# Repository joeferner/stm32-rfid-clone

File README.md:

# STM32 RFID Reader / Writer

Currently only reading is working.

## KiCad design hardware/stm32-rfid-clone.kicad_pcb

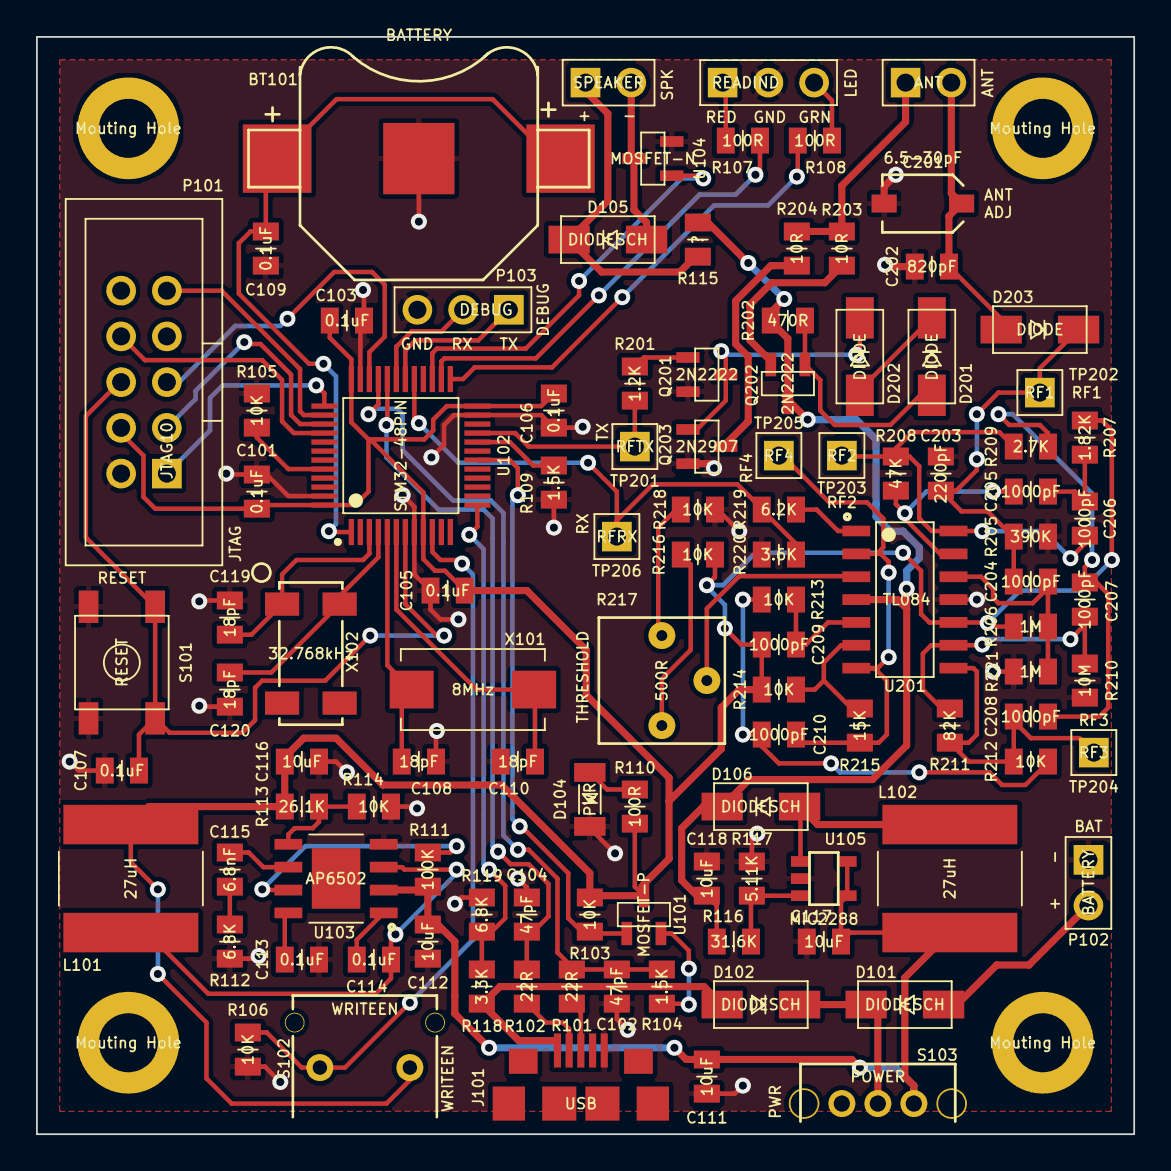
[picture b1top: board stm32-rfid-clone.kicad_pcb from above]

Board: 2 copper layers, 61.0 x 61.0 mm, 112 parts (0 on the bottom side), 73 nets.

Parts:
BT101: BATTERY; KEYSTONE-3000
C101, C103, C105, C106, C107, C109, C113, C114: 0.1uF; CAPC2012X100N
C102, C104: 47pF; CAPC2012X100N
C108, C110, C119, C120: 18pF; CAPC2012X100N
C111, C112, C116, C117, C118: 10uF; CAPC2012X100N
C115: 6.8nF; CAPC2012X100N
C201: 6.5-30pF; MURATA-TZC3
C202: 820pF; CAPC2012X100N
C203: 2200pF; CAPC2012X100N
C204, C205, C206, C207, C208, C209, C210: 1000pF; CAPC2012X100N
D101, D102, D105, D106: DIODESCH; DIOM5226X220N
D104: PWR; LEDC3216X100N
D201, D202, D203: DIODE; DIOM5226X220N
J101: USB; JST_UB-MC5BR3-SD204-4S-NMP
L101, L102: 27uH; IND_ASPI-8040S-680M-T
M101, M102, M103, M104: Mouting Hole; MTGNP565H328Z565P
P101: JTAG10; SHDRV10W66P254_2X5_2035X870X609P
P102: BATTERY; HDRV2W66P254_1X2_508X249X838P
P103: DEBUG; HDRV3W66P254_1X3_762X249X838P
P104: READIND; HDRV3W66P254_1X3_762X249X838P
P105: SPEAKER; HDRV2W66P254_1X2_508X249X838P
P201: ANT; HDRV2W66P254_1X2_508X249X838P
Q201, Q202: 2N2222; SOT95P237X112_123-3N
Q203: 2N2907; SOT95P237X112_123-3N
R101, R102: 22R; RESC2012X100N
R103, R105, R106, R114, R212, R213, R214, R216, R218: 10K; RESC2012X100N
R104, R109: 1.5K; RESC2012X100N
R107, R108, R110: 100R; RESC2012X100N
R111: 100K; RESC2012X100N
R112, R119: 6.8K; RESC2012X100N
R113: 26.1K; RESC2012X100N
R115: ?; RESC2012X100N
R116: 31.6K; RESC2012X100N
R117: 5.11K; RESC2012X100N
R118: 3.3K; RESC2012X100N
R201: 1.2K; RESC2012X100N
R202: 470R; RESC2012X100N
R203, R204: 10R; RESC2012X100N
R205: 390K; RESC2012X100N
R206, R221: 1M; RESC2012X100N
R207: 1.82K; RESC2012X100N
R208: 47K; RESC2012X100N
R209: 2.7K; RESC2012X100N
R210: 10M; RESC2012X100N
R211: 82K; RESC2012X100N
R215: 15K; RESC2012X100N
R217: 500R; COPAL-CT6EP
R219: 6.2K; RESC2012X100N
R220: 3.6K; RESC2012X100N
S101: RESET; CKCOMP-PTS525SM10SMTR
S102: WRITEEN; APEM-MJTP1129B
S103: POWER; CKCOMP-OS102011MA1QN1
TP201: RFTX; HDRV1W66P254_1X1_254X249X838P
TP202: RF1; HDRV1W66P254_1X1_254X249X838P
TP203: RF2; HDRV1W66P254_1X1_254X249X838P
TP204: RF3; HDRV1W66P254_1X1_254X249X838P
TP205: RF4; HDRV1W66P254_1X1_254X249X838P
TP206: RFRX; HDRV1W66P254_1X1_254X249X838P
U101: MOSFET-P; SOT95P237X112_123-3N
U102: STM32-48PIN; QFP50P900X900X160-48N
U103: AP6502; SOIC127P600X150-9N
U104: MOSFET-N; SOT95P237X112_123-3N
U105: MIC2288; SOT95P280X100-5N
U201: TL084; SOIC127P600X175-14N
X101: 8MHz; XTAL8045X200N
X102: 32.768kHz; SOJ550P370X240-4N

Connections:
+3.3V: C101.1, C103.1, C105.1, C106.1, C116.1, C209.1, L101.1, P101.4, R103.1, R110.1, R113.1, R206.1, R207.1, R214.2, R216.1, S102.1, U101.3, U102.9, U102.24, U102.36, U102.48, U201.10
+9V: C118.1, D106.2, Q202.3, R115.1, R116.1, R202.1, U201.4
/BEEP: U102.27, U104.1
/JNTRST: P101.8, U102.40
/JTCK: P101.1, U102.37
/JTDI: P101.9, U102.38
/JTDO: P101.3, U102.39
/JTMS: P101.5, U102.34
/LEDGRN: R108.1, U102.25
/LEDRED: R107.1, U102.26
/RF/RX: R219.2, R220.1, TP206.1, U102.29
/RF/TX: R201.2, TP201.1, U102.21
/USARTRX: P103.2, U102.31
/USARTTX: P103.1, U102.30
/USBDET: R118.2, R119.1, U102.13
/USBDIS: R103.2, U101.1, U102.18
/USBDM: C104.1, R102.1, U102.32
/USBDP: C102.1, R101.1, R104.2, U102.33
/VBAT: BT101.1, C109.1, U102.1
/VIN: C111.1, C112.1, C117.1, L102.2, R111.1, S103.3, U103.2, U105.4, U105.5
/VUSB: D102.1, J101.1, R118.1
/WRITEEN: R106.1, S102.2, U102.10
/nRST: C107.1, P101.6, S101.3, S101.4, U102.7
GNDPWR: BT101.2, C101.2, C102.2, C103.2, C104.2, C105.2, C106.2, C107.2, C108.2, C109.2, C110.2, C111.2, C112.2, C113.2, C116.2, C117.2, C118.2, C119.2, C120.2, C201.2, C202.2, C203.2, D104.2, J101.5, P101.2, P102.1, P103.3, P104.2, Q201.2, Q203.2, R105.2, R106.2, R109.2, R112.2, R114.2, R117.2, R119.2, R205.2, R210.1, R218.2, R220.2, R221.2, S101.1, S101.2, U102.8, U102.23, U102.35, U102.47, U103.4, U104.2, U105.2, U201.11
unnamed: C108.1, U102.5, X101.1
unnamed: C110.1, U102.6, X101.2
unnamed: C113.1, U103.8
unnamed: C114.1, U103.1
unnamed: C114.2, L101.2, U103.3
unnamed: C115.1, U103.6
unnamed: C115.2, R112.1
unnamed: C119.1, U102.3, X102.1
unnamed: C120.1, U102.4, X102.4
unnamed: C201.1, C202.1, D203.1, P201.2
unnamed: C203.1, C204.1, D203.2, R205.1, TP202.1
unnamed: C204.2, R206.2, R221.1, U201.12
unnamed: C205.1, R208.1, U201.13
unnamed: C205.2, C206.1, R207.2
unnamed: C206.2, R208.2, R209.1, TP203.1, U201.14
unnamed: C207.1, C208.1, R209.2
unnamed: C207.2, R210.2, R211.1, U201.9
unnamed: C208.2, R211.2, R212.1, TP204.1, U201.8
unnamed: C209.2, R213.2, U201.5
unnamed: C210.1, R212.2, R213.1
unnamed: C210.2, R215.1, TP205.1, U201.2, U201.7
unnamed: D101.1, P102.2
unnamed: D101.2, D102.2, S103.2
unnamed: D104.1, R110.2
unnamed: D105.1, P105.2, U104.3
unnamed: D105.2, P105.1, R115.2
unnamed: D106.1, L102.1, U105.1
unnamed: D201.1, Q202.1, R202.2
unnamed: D201.2, D202.1
unnamed: D202.2, Q201.3, Q203.1
unnamed: J101.2, R102.2
unnamed: J101.3, R101.2
unnamed: P104.1, R107.2
unnamed: P104.3, R108.2
unnamed: P201.1, R203.2, R204.1
unnamed: Q201.1, R201.1
unnamed: Q202.2, R203.1
unnamed: Q203.3, R204.2
unnamed: R104.1, U101.2
unnamed: R105.1, U102.44
unnamed: R109.1, U102.20
unnamed: R111.2, U103.7
unnamed: R113.2, R114.1, U103.5
unnamed: R116.2, R117.1, U105.3
unnamed: R214.1, R215.2, U201.6
unnamed: R216.2, R217.3
unnamed: R217.1, R218.1
unnamed: R217.2, U201.3
unnamed: R219.1, U201.1

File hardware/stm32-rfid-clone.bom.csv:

Id	Designator	Package	Quantity	Designation	Supplier and ref
1	BT101	stm32:KEYSTONE-3000	1	BATTERY	NA
2	C101,C103,C105,C106,C107,C109,C113,C114	stm32:CAPC2012X100N	8	0.1uF	10
3	C102,C104	stm32:CAPC2012X100N	2	48pF	446
4	C108,C110,C119,C120	stm32:CAPC2012X100N	4	18pF	388
5	C111,C112,C116,C117,C118	stm32:CAPC2012X100N	5	10uF	389
6	C115	stm32:CAPC2012X100N	1	6.8nF	492
7	C201	stm32:MURATA-TZC3	1	6.5-30pF	514
8	C202,C204,C205,C206,C207,C208,C209,C210	stm32:CAPC2012X100N	8	1000pF	520
9	C203	stm32:CAPC2012X100N	1	2200pF	521
10	D101,D102,D105,D106	stm32:DIOM5226X220N	4	DIODESCH	273
11	D104	stm32:LEDC3216X100N	1	PWR	176
12	D201,D202,D203	stm32:DIOM5226X220N	3	DIODE	518
13	J101	stm32:JST_UB-MC5BR3-SD204-4S-NMP	1	USB	274
14	L101,L102	stm32:IND_ASPI-8040S-680M-T	2	27uH	513
15	M101,M102,M103,M104	stm32:MTGNP565H328Z565P	4	Mouting Hole	NA
16	P101	stm32:SHDRV10W66P254_2X5_2035X870X609P	1	JTAG10	NA
17	P102	stm32:HDRV2W66P254_1X2_508X249X838P	1	BATTERY	NA
18	P103	stm32:HDRV3W66P254_1X3_762X249X838P	1	DEBUG	NA
19	P104	stm32:HDRV3W66P254_1X3_762X249X838P	1	READIND	NA
20	P105	stm32:HDRV2W66P254_1X2_508X249X838P	1	SPEAKER	NA
21	P201	stm32:HDRV2W66P254_1X2_508X249X838P	1	ANT	NA
22	Q201,Q202	stm32:SOT95P237X112_123-3N	2	2N2222	168
23	Q203	stm32:SOT95P237X112_123-3N	1	2N2907	515
24	R101,R102	stm32:RESC2012X100N	2	22R	49
25	R103,R105,R106,R114,R212,R213,R214,R216,R218	stm32:RESC2012X100N	9	10K	299
26	R104,R109	stm32:RESC2012X100N	2	1.5K	391
27	R107,R108,R110	stm32:RESC2012X100N	3	100R	300
28	R111	stm32:RESC2012X100N	1	100K	392
29	R112,R119	stm32:RESC2012X100N	2	6.8K	491
30	R113	stm32:RESC2012X100N	1	26.1K	522
31	R115	stm32:RESC2012X100N	1	?	
32	R116	stm32:RESC2012X100N	1	31.6K	523
33	R117	stm32:RESC2012X100N	1	5.11K	524
34	R118	stm32:RESC2012X100N	1	3.3K	525
35	R201	stm32:RESC2012X100N	1	1.2K	526
36	R202	stm32:RESC2012X100N	1	470R	527
37	R203,R204	stm32:RESC2012X100N	2	10R	528
38	R205	stm32:RESC2012X100N	1	390K	529
39	R206,R221	stm32:RESC2012X100N	2	1M	530
40	R207	stm32:RESC2012X100N	1	1.82K	531
41	R208	stm32:RESC2012X100N	1	47.5K	497
42	R209	stm32:RESC2012X100N	1	2.7K	532
43	R210	stm32:RESC2012X100N	1	10M	533
44	R211	stm32:RESC2012X100N	1	82.5K	534
45	R215	stm32:RESC2012X100N	1	15K	535
46	R217	stm32:COPAL-CT6EP	1	500R	407
47	R219	stm32:RESC2012X100N	1	6.2K	536
48	R220	stm32:RESC2012X100N	1	3.6K	537
49	S101	stm32:CKCOMP-PTS525SM10SMTR	1	RESET	275
50	S103	stm32:CKCOMP-OS102011MA1QN1	1	POWER	519
51	TP201	stm32:HDRV1W66P254_1X1_254X249X838P	1	RFTX	NA
52	TP202	stm32:HDRV1W66P254_1X1_254X249X838P	1	RF1	NA
53	TP203	stm32:HDRV1W66P254_1X1_254X249X838P	1	RF2	NA
54	TP204	stm32:HDRV1W66P254_1X1_254X249X838P	1	RF3	NA
55	TP205	stm32:HDRV1W66P254_1X1_254X249X838P	1	RF4	NA
56	TP206	stm32:HDRV1W66P254_1X1_254X249X838P	1	RFRX	NA
57	U101	stm32:SOT95P237X112_123-3N	1	MOSFET-P	293
58	U102	stm32:QFP50P900X900X160-48N	1	STM32-48PIN	375
59	U103	stm32:SOIC127P600X150-9N	1	AP6502	475
60	U104	stm32:SOT95P237X112_123-3N	1	MOSFET-N	37
61	U105	stm32:SOT95P280X100-5N	1	MIC2288	512
62	U201	stm32:SOIC127P600X175-14N	1	TL084	516
63	X101	stm32:XTAL8045X200N	1	8MHz	488
64	S102	stm32:APEM-MJTP1129B	1	WRITEEN	517
65	X102	stm32:SOJ550P370X240-4N	1	32.768kHz	280

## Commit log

2013-11-26 initial
2013-11-26 added gcc_stm32.cmake
2013-11-26 configure timer
2013-11-26 turn tx on and off
2013-11-29 working 128kHz
2013-12-02 read exti
2013-12-03 working usb coms
2013-12-03 working usb report send
2013-12-04 send coms
2013-12-04 working data capture
2013-12-08 refactor rx tx
2013-12-08 remove tim1 ch2
2013-12-09 working dma
2013-12-09 trying to get dma working
2013-12-09 better dma
2013-12-10 rename variables
2013-12-10 working rfid read
2013-12-10 added readme
2013-12-11 move firmware
2013-12-11 added kicad-library subtree
2013-12-11 initial kicad
2013-12-11 initial schematic work
2013-12-12 update to lib list
2013-12-12 add usb and gnd
2013-12-12 added usb back
2013-12-12 update usb
2013-12-12 bring back gnd
2013-12-12 fixed gnd
2013-12-13 added 9V to 3.3V
2013-12-13 removed whitespace
2013-12-13 initial rf
2013-12-13 rf done
2013-12-13 added spst renamed btn_spst
2013-12-13 added read indicator
2013-12-13 reannotate
2013-12-14 draft complete schematic
2013-12-14 added footprint assoc.
2013-12-15 added image of hid reader
2013-12-15 updates to libs
2013-12-16 initial mechanical
2013-12-16 update docs
2013-12-17 added battery
2013-12-19 more
2013-12-20 mods
2013-12-20 added SOT95P280X100-5N
2013-12-20 first move
2013-12-20 changed mods and libs to better represent pins
2013-12-27 pcb layout
2013-12-27 edge cuts
2013-12-28 increase track widths for power
2013-12-28 moved labels
2014-01-05 update values
2014-01-06 update schematic
2014-01-15 2014-01-14
2014-01-28 usb detect
2014-01-28 update to values
2014-04-14 add initial write functionality
2014-04-17 sump
2014-04-17 add notes
2014-04-18 more sump
2014-04-18 more sump work
2014-04-18 sump working
2014-04-18 better unit tests
2014-04-18 fix build
2014-04-19 turn on debug led
2014-04-20 more em4x05 work
2014-04-21 tweeks
2014-04-21 ring buffer test
2014-04-21 fix compiler warnings
2014-04-21 reformat
2014-05-12 switch debug output to be eeworkbench compatible
2014-05-12 buffer eeworkbench data
2014-05-12 output code using eeworkbench compatible string
2014-05-15 turn off tx on off
2014-05-15 removed tx state
2014-05-24 docs and logic analyzer
